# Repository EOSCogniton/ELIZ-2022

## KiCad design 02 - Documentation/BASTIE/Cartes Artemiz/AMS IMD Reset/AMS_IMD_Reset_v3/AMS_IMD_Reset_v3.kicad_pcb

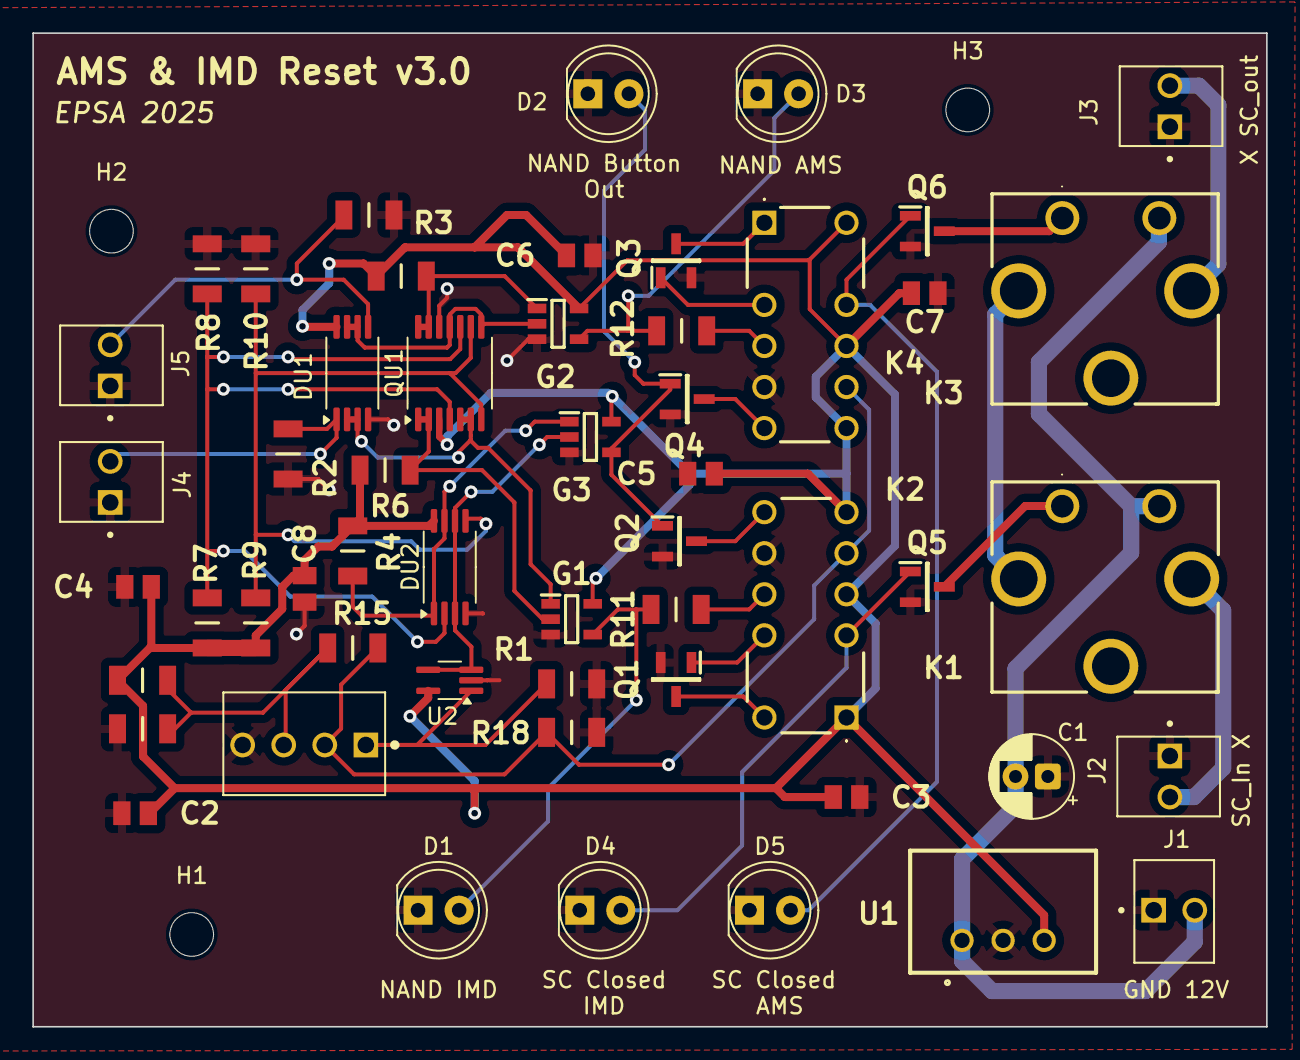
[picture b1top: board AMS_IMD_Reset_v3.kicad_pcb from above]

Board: 2 copper layers, 76.3 x 61.5 mm, 56 parts (0 on the bottom side), 34 nets.

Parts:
C1: C; CP_Radial_D5.0mm_P2.00mm
C2, C3, C4, C5, C6, C7, C8: 1u; CAPC2012X130N
D1, D2, D3, D4, D5: LED; LED_D5.0mm
DU1, DU2: Opamp_Dual; TSSOP-8_4.4x3mm_P0.65mm
G1, G2: Gate NAND SN74AHCT1G00DBVR; SOT95P280X145-5N
G3: Gate AND SN74AHCT1G08DBVR; SOT95P280X145-5N
H1, H2, H3: MountingHole; MountingHole_2.7mm_M2.5
J1, J2, J3, J4, J5: 2P Droit 2-11-2022; MOLEX_22-11-2022
J7: 4P Droit 22-11-2042; MOLEX_22-11-2042
K1, K3: Relais PCB; CP112V
K2, K4: Bistable V23079B1201B301; V23079B1201B301
Q1, Q2, Q3, Q4, Q5, Q6: NMOS SQ2348ES-T1_GE3; SOT95P237X112-3N
QU1: Opamp_Quad; TSSOP-14_4.4x5mm_P0.65mm
R1, R2, R3: 500k; RESC3216X70N
R4, R5, R6: 10k; RESC3216X70N
R7, R10: 82k; RESC3216X70N
R8, R9: 12k; RESC3216X70N
R11, R12: 500; RESC3216X70N
R15: 3k9; RESC3216X70N
R16, R17: 8k2; RESC3216X70N
R18: 100k; RESC3216X70N
U1: Alim LP TSR_0.5-2450; TSR-0.5-2433
U2: SOT-353_SC-70-5_Handsoldering

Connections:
+5V: C2.1, C3.2, C4.2, C5.2, C6.1, C7.1, C8.1, DU1.8 (V+), DU2.8 (V+), G1.5 (VCC), G2.5 (VCC), G3.5 (VCC), K2.1 (COIL1), K2.4 (COM_1), K2.6 (COIL2), K4.7 (COIL2), K4.9 (COM_2), K4.12 (COIL1), QU1.3 (V+), R4.1, R5.2, R6.1, R7.2, R9.2, R16.2, U1.3 (+VOUT), U2.5 (V+)
+12V: C1.2, J1.2, K1.5, K3.5, U1.1 (+VIN)
/0.75V: DU2.2 (-), QU1.4 (-), QU1.10 (-), R7.1, R8.2
/4.25V: DU2.5 (+), QU1.7 (+), QU1.9 (+), R9.1, R10.2
/AMS_OK: DU1.6 (-), DU1.7, G2.2, QU1.8 (-), QU1.11 (+)
/AMS_SCS_Compliance: G2.1, QU1.13, QU1.14, R5.1
/Button_Input: J7.2, K2.5 (Set_1), K4.8 (Set_2), R15.1, R18.1
/Button_Input_SCS: J7.3, R15.2, R16.1, R17.2
/Button_Output: DU2.3 (+), DU2.6 (-), G3.2, U2.3 (-), U2.4
/Button_Output_SCS_Compliance: DU2.1, DU2.7, G3.1, R4.2
/IMD_OK: DU1.2 (-), DU1.3, G1.1, QU1.5 (+), QU1.6 (-)
/IMD_SCS_Compliance: G1.2, QU1.1, QU1.2, R6.2
/Raw_AMS_OK: DU1.5 (+), J5.2, R3.1
/Raw_Button_Output: J7.1, R1.1, U2.1 (+)
/Raw_IMD_OK: DU1.1 (+), J4.2, R2.1
/SC in: J2.2, K1.4
/SC out: J3.2, K3.4
/SC_Closed_AMS: D5.2 (A), K4.10 (Reset_2), Q6.1
/SC_Closed_IMD: D4.2 (A), K2.3 (Reset_1), Q5.1
GND: C1.1, C2.2, C3.1, C4.1, C5.1, C6.2, C7.2, C8.2, D1.1 (K), D2.1 (K), D3.1 (K), D4.1 (K), D5.1 (K), DU1.4 (V-), DU2.4 (V-), G1.3 (GND), G2.3 (GND), G3.3 (GND), J1.1, J2.1, J3.1, J4.1, J5.1, J7.4, K2.8 (Set_2), K4.5 (Set_1), Q1.2, Q2.2, Q3.2, Q4.2, Q5.2, Q6.2, QU1.12 (V-), R1.2, R2.2, R3.2, R8.1, R10.1, R17.1, R18.2, U1.2 (GND), U2.2 (V-)
unnamed: D1.2 (A), G1.4, R11.1
unnamed: D2.2 (A), G3.4, Q2.1, Q4.1
unnamed: D3.2 (A), G2.4, R12.1
unnamed: K1.1, Q5.3
unnamed: K1.2, K3.2
unnamed: K2.12 (COIL1), Q1.3
unnamed: K2.7 (COIL2), Q2.3
unnamed: K2.9 (COM_2), R11.2
unnamed: K2.10 (Reset_2), Q1.1
unnamed: K3.1, Q6.3
unnamed: K4.1 (COIL1), Q3.3
unnamed: K4.6 (COIL2), Q4.3
unnamed: K4.4 (COM_1), R12.2
unnamed: K4.3 (Reset_1), Q3.1

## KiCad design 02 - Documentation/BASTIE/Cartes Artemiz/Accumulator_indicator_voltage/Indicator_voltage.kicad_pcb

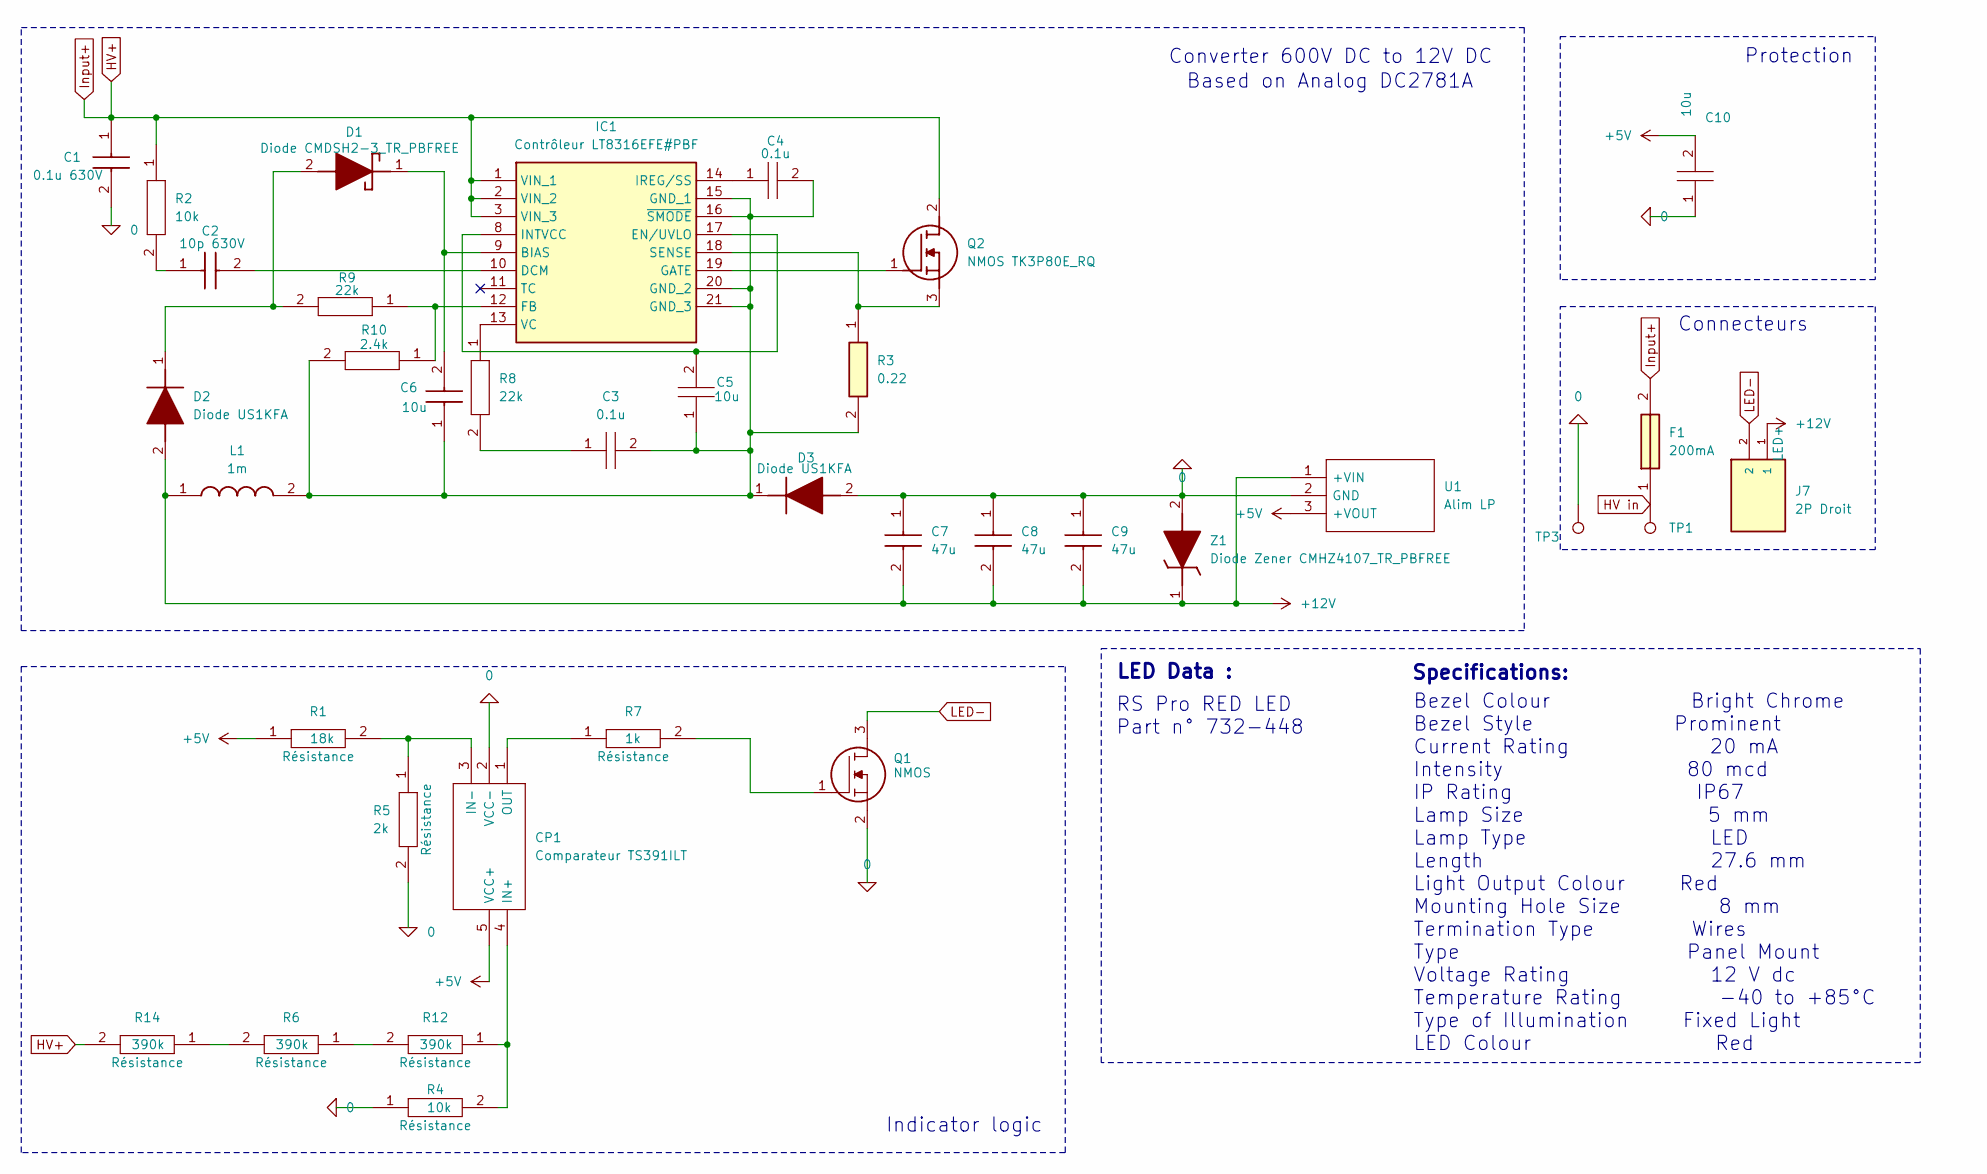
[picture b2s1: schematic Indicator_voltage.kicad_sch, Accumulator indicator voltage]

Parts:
C1: 0.1u 630V; CAPC4532X200N; Mouser Part Number 81-GCJ43DR72J104KX1L
C2: 10p 630V; CAPC3216X100N; Mouser Part Number 81-GRM31A5C2J100JW1D
C3, C4: 0.1u; CAPC2012X130N; Manufacturer_Part_Number 0805Y1000104JXT
C5, C10: 10u; CAPC2012X130N; Manufacturer_Part_Number 0805Y1000104JXT
C6: 10u; GRM31x; Manufacturer_Part_Number GRM31CR71E106KA12L; Mouser Part Number 81-GRM31CR71E106KA12
C7, C8, C9: 47u; CAPC3225X270N; Mouser Part Number 81-GRM32ER61C476KE5K
CP1: Comparateur TS391ILT; SOT95P280X145-5N; Manufacturer_Part_Number TS391ILT; Mouser Part Number 511-TS391IL
D1: Diode CMDSH2-3_TR_PBFREE; SOD2512X110N; Mouser Part Number 610-CMDSH2-3
D2, D3: Diode US1KFA; SODFL3618X143N; Mouser Part Number 512-US1KFA
F1: 200mA; 0ADAP0200RE; Mouser Part Number 530-0ADAP0200-RE
IC1: Contrôleur LT8316EFE#PBF; LT8315EFEPBF; Mouser Part Number 584-LT8316EFE#PBF
J7: 2P Droit 2-11-2022; MOLEX_22-11-2022; PARTREV BD8; Mouser Part Number 538-22-11-2022
L1: 1m; WE-PD_1260_1245_1280_121054; Mouser Part Number 710-7447709102
Q1: NMOS SQ2348ES-T1_GE3; SOT95P237X112-3N; Manufacturer_Part_Number SQ2348ES-T1_GE3; Mouser Part Number 781-SQ2348ES-T1_GE3
Q2: NMOS TK3P80E_RQ; TK3P80ERQ; Manufacturer_Part_Number TK3P80E,RQ
R1: 18k; RESC3216X70N; Manufacturer_Part_Number RK73H2BLTDD2152F; Mouser Part Number N/A
R2, R4: 10k; RESC3216X70N; Manufacturer_Part_Number RK73H2BLTDD2152F; Mouser Part Number N/A
R3: 0.22; RESC1608X55N; Mouser Part Number 754-RL0816S-R22-F
R5: 2k; RESC3216X70N; Manufacturer_Part_Number RK73H2BLTDD2152F; Mouser Part Number N/A
R6, R12, R14: 390k; RESC3216X70N; Manufacturer_Part_Number RK73H2BLTDD2152F; Mouser Part Number N/A
R7: 1k; RESC3216X70N; Manufacturer_Part_Number RK73H2BLTDD2152F; Mouser Part Number N/A
R8, R9: 22k; RESC3216X70N; Manufacturer_Part_Number RK73H2BLTDD2152F; Mouser Part Number N/A
R10: 2.4k; RESC3216X70N; Manufacturer_Part_Number RK73H2BLTDD2152F; Mouser Part Number N/A
TP1, TP3: type="R" model="TestPoint" lib=""; SolderWire-2.5sqmm_1x01_D2.4mm_OD3.6mm
U1: Alim LP TSR_0.5-2450; TSR-0.5-2433; Manufacturer_Part_Number TSR 0.5-2450; Mouser Part Number 495-TSR0.5-2450
Z1: Diode Zener CMHZ4107_TR_PBFREE; SOD3816X135N; Manufacturer_Part_Number CMHZ4107 TR PBFREE

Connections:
0: C1.2, C7.1, C8.1, C9.1, C10.1, CP1.2 (VCC-), D3.2 (A), Q1.2, R4.1, R5.2, TP3.1, U1.2 (GND), Z1.2 (A)
+5V: C10.2, CP1.5 (VCC+), R1.1, U1.3 (+VOUT)
+12V: C7.2, C8.2, C9.2, D2.2 (A), J7.1, L1.1, U1.1 (+VIN), Z1.1 (K)
HV in: F1.1, TP1.1
HV+: C1.1, F1.2, IC1.1 (VIN_1), IC1.2 (VIN_2), IC1.3 (VIN_3), Q2.2 (D), R2.1, R14.2
LED-: J7.2, Q1.3
unnamed: C2.1, R2.2
unnamed: C3.1, R8.2
unnamed: CP1.4 (IN+), R4.2, R12.1
unnamed: CP1.3 (IN-), R1.2, R5.1
unnamed: CP1.1 (OUT), R7.1
unnamed: D1.2 (A), D2.1 (K), R9.2
unnamed: C6.2, D1.1 (K), IC1.9 (BIAS)
unnamed: C3.2, C4.2, C5.1, C6.1, D3.1 (K), IC1.15 (GND_1), IC1.16 (~SMODE), IC1.20 (GND_2), IC1.21 (GND_3), L1.2, R3.2, R10.2
unnamed: C2.2, IC1.10 (DCM)
unnamed: C5.2, IC1.8 (INTVCC), IC1.17 (EN/UVLO)
unnamed: IC1.12 (FB), R9.1, R10.1
unnamed: IC1.19 (GATE), Q2.1 (G)
unnamed: C4.1, IC1.14 (IREG/SS)
unnamed: IC1.18 (SENSE), Q2.3 (S), R3.1
unnamed: IC1.13 (VC), R8.1
unnamed: Q1.1, R7.2
unnamed: R6.1, R12.2
unnamed: R6.2, R14.1

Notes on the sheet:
Protection
Based on Analog DC2781A
RS Pro RED LED Part n° 732-448
Indicator logic
LED Data :
Specifications:
Connecteurs
Converter 600V DC to 12V DC
Bezel Colour Bright Chrome Bezel Style Prominent Current Rating 20 mA Intensity 80 mcd IP Rating IP67 Lamp Size 5 mm Lamp Type LED Length 27.6 mm Light Output Colour Red Mounting Hole Size 8 mm Termination Type Wires Type Panel Mount Voltage Rating 12 V dc Temperature Rating -40 to +85°C Type of Il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

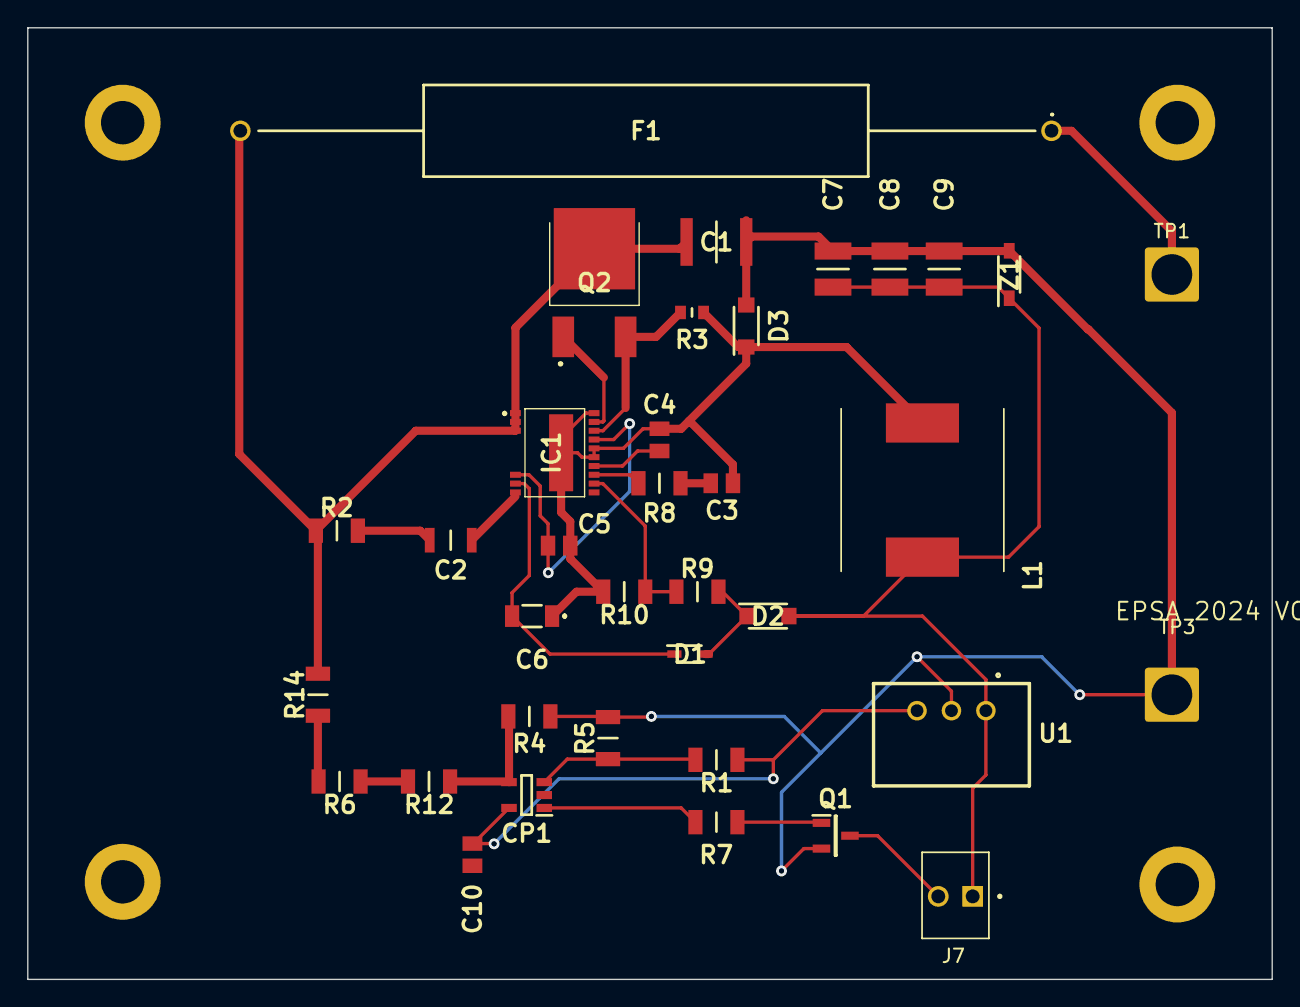
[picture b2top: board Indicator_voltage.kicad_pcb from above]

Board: 2 copper layers, 91.8 x 70.2 mm, 36 parts (0 on the bottom side), 24 nets.

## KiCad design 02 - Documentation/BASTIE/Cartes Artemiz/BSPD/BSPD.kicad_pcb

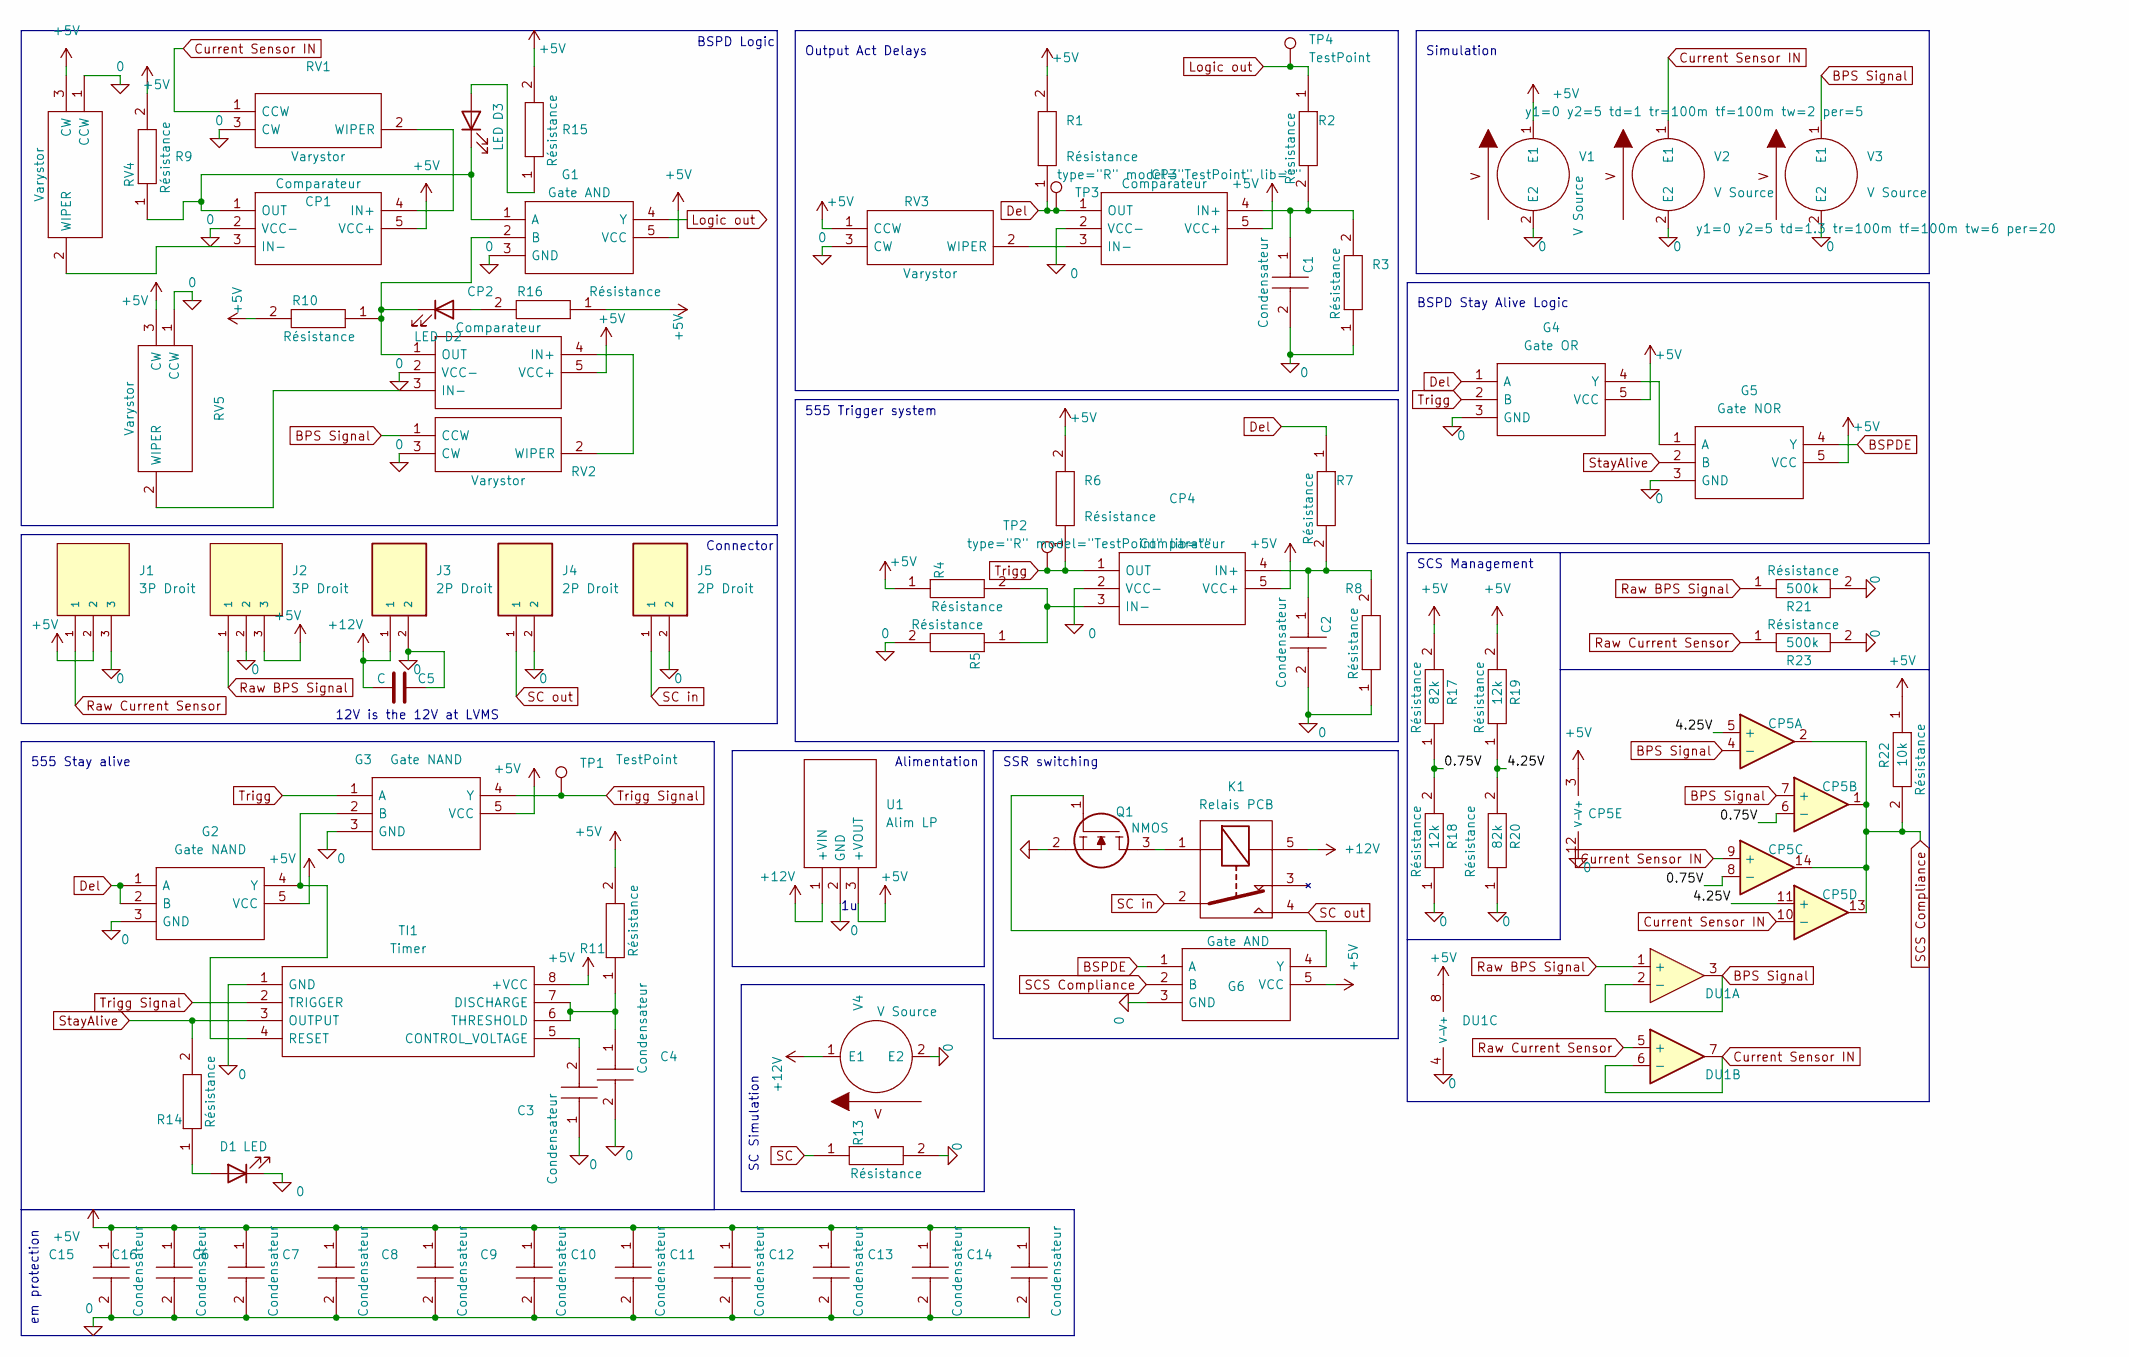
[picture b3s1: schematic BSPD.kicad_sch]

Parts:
C1, C2, C3, C4, C6, C7, C8, C9, C10, C11, C12, C13, C14, C15, C16: Condensateur 0805Y1000104JXT; CAPC2012X130N; Manufacturer_Part_Number 0805Y1000104JXT
C5: C; CP_Radial_D5.0mm_P2.00mm
CP1, CP2, CP3, CP4: Comparateur TS391ILT; SOT95P280X145-5N; Manufacturer_Part_Number TS391ILT; Mouser Part Number 511-TS391IL
CP5: Opamp_Quad; TSSOP-14_4.4x5mm_P0.65mm; Manufacturer_Part_Number LMV339IPWR; Mouser Part Number 595-LMV339IPWR
D1, D2, D3: LED; LED_D5.0mm
DU1: Opamp_Dual; TSSOP-8_4.4x3mm_P0.65mm; Manufacturer_Part_Number TLV9062QPWRQ1; Mouser Part Number 595-TLV9062QPWRQ1
G1, G6: Gate AND SN74AHCT1G08DBVR; SOT95P280X145-5N; Manufacturer_Part_Number SN74AHCT1G08DBVR; Mouser Part Number 595-SN74AHCT1G08DBVR
G2, G3: Gate NAND SN74AHCT1G00DBVR; SOT95P280X145-5N; Manufacturer_Part_Number SN74AHCT1G00DBVR; Mouser Part Number 595-SN74AHCT1G00DBVR
G4: Gate OR SN74AHCT1G32DBVR; SOT95P280X145-5N; Manufacturer_Part_Number SN74AHCT1G32DBVR; Mouser Part Number 595-SN74AHCT1G32DBVR
G5: Gate NOR SN74AHCT1G02DBVR; SOT95P280X145-5N; Manufacturer_Part_Number SN74AHCT1G02DBVR; Mouser Part Number 595-SN74AHCT1G02DBVR
J1, J2: 3P Droit 22-11-2032; MOLEX_22-11-2032; PARTREV BD8
J3, J4, J5: 2P Droit 2-11-2022; MOLEX_22-11-2022; PARTREV BD8
K1: Relais PCB; CP112V; Mouser Part Number 769-CP1-12V
Q1: NMOS SQ2348ES-T1_GE3; SOT95P237X112-3N; Manufacturer_Part_Number SQ2348ES-T1_GE3; Mouser Part Number 781-SQ2348ES-T1_GE3
R1, R2, R3, R4, R5, R6, R7, R8, R9, R10, R11, R13, R14, R15, R16: Résistance RK73H2BLTDD2152F; RESC3216X70N; Manufacturer_Part_Number RK73H2BLTDD2152F; Mouser Part Number N/A
R17, R20: 82k; RESC3216X70N; Manufacturer_Part_Number RK73H2BLTDD2152F; Mouser Part Number N/A
R18, R19: 12k; RESC3216X70N; Manufacturer_Part_Number RK73H2BLTDD2152F; Mouser Part Number N/A
R21, R23: 500k; RESC3216X70N; Manufacturer_Part_Number RK73H2BLTDD2152F; Mouser Part Number N/A
R22: 10k; RESC3216X70N; Manufacturer_Part_Number RK73H2BLTDD2152F; Mouser Part Number N/A
RV1, RV2, RV3, RV4, RV5: Varystor 3296Y-1-223LF; 3296Y1223LF; Manufacturer_Part_Number 3296Y-1-223LF; Mouser Part Number 652-3296Y-1-223LF
TI1: Timer 555 LM555CMX_NOPB; DIP-8_W7.62mm_Socket; Manufacturer_Part_Number LM555CMX/NOPB; Mouser Part Number 926-LM555CMX/NOPB
TP1, TP4: TestPoint; TestPoint_Pad_D2.0mm
TP2, TP3: type="R" model="TestPoint" lib=""; TestPoint_Pad_D2.0mm
U1: Alim LP TSR_0.5-2450; TSR-0.5-2433; Manufacturer_Part_Number TSR 0.5-2450; Mouser Part Number 495-TSR0.5-2450
V1: 5
V2, V3: VSOURCE
V4: 12

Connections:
0: C1.2, C2.2, C3.1, C4.2, C5.2, C6.2, C7.2, C8.2, C9.2, C10.2, C11.2, C12.2, C13.2, C14.2, C15.2, C16.2, CP1.2 (VCC-), CP2.2 (VCC-), CP3.2 (VCC-), CP4.2 (VCC-), CP5.12 (V-), D1.1 (K), DU1.4 (V-), G1.3 (GND), G2.3 (GND), G3.3 (GND), G4.3 (GND), G5.3 (GND), G6.3 (GND), J1.3, J2.2, J3.2, J4.2, J5.2, R3.1, R5.2, R8.1, R18.1, R20.1, R21.2, R23.2, RV1.3 (CW), RV2.3 (CW), RV3.3 (CW), RV4.1 (CCW), RV5.1 (CCW), TI1.1 (GND), U1.2 (GND)
+5V: C6.1, C7.1, C8.1, C9.1, C10.1, C11.1, C12.1, C13.1, C14.1, C15.1, C16.1, CP1.5 (VCC+), CP2.5 (VCC+), CP3.5 (VCC+), CP4.5 (VCC+), CP5.3 (V+), DU1.8 (V+), G1.5 (VCC), G2.5 (VCC), G3.5 (VCC), G4.5 (VCC), G5.5 (VCC), G6.5 (VCC), J1.2, J2.3, R1.2, R4.1, R6.2, R9.2, R10.2, R11.2, R15.2, R16.1, R17.2, R19.2, R22.1, RV3.1 (CCW), RV4.3 (CW), RV5.3 (CW), TI1.8 (+VCC), U1.3 (+VOUT)
+12V: C5.1, J3.1, K1.5, U1.1 (+VIN), V4.1 (E1)
/0.75V: CP5.6 (-), CP5.8 (-), R17.1, R18.2
/4.25V: CP5.5 (+), CP5.11 (+), R19.1, R20.2
BPS Signal: CP5.4 (-), CP5.7 (+), DU1.2 (-), DU1.3, RV2.1 (CCW), V3.1 (E1)
BSPDE: G5.4 (Y), G6.1 (A)
Current Sensor IN: CP5.9 (+), CP5.10 (-), DU1.6 (-), DU1.7, RV1.1 (CCW), V2.1 (E1)
Del: CP3.1 (OUT), G2.1 (A), G2.2 (B), G4.1 (A), R1.1, R7.1, TP3.1
GND: Q1.2
Logic out: G1.4 (Y), R2.1, TP4.1
unnamed: CP1.4 (IN+), RV1.2 (WIPER)
unnamed: CP1.3 (IN-), RV4.2 (WIPER)
unnamed: CP1.1 (OUT), D3.1 (K), G1.1 (A), R9.1
unnamed: CP2.4 (IN+), RV2.2 (WIPER)
unnamed: CP2.3 (IN-), RV5.2 (WIPER)
unnamed: CP2.1 (OUT), D2.1 (K), G1.2 (B), R10.1
unnamed: C1.1, CP3.4 (IN+), R2.2, R3.2
unnamed: CP3.3 (IN-), RV3.2 (WIPER)
unnamed: C2.1, CP4.4 (IN+), R7.2, R8.2
unnamed: CP4.3 (IN-), R4.2, R5.1
unnamed: D1.2 (A), R14.1
unnamed: D2.2 (A), R16.2
unnamed: D3.2 (A), R15.1
unnamed: G2.4 (Y), G3.2 (B), TI1.4 (RESET)
unnamed: G4.4 (Y), G5.1 (A)
unnamed: G6.4 (Y), Q1.1
unnamed: K1.1, Q1.3
unnamed: C3.2, TI1.5 (CONTROL_VOLTAGE)
unnamed: C4.1, R11.1, TI1.6 (THRESHOLD), TI1.7 (DISCHARGE)
Raw BPS Signal: DU1.1 (+), J2.1, R21.1
Raw Current Sensor: DU1.5 (+), J1.1, R23.1
SC in: J5.1, K1.2
SC out: J4.1, K1.4
SCS Compliance: CP5.1, CP5.2, CP5.13, CP5.14, G6.2 (B), R22.2
StayAlive: G5.2 (B), R14.2, TI1.3 (OUTPUT)
Trigg: CP4.1 (OUT), G3.1 (A), G4.2 (B), R6.1, TP2.1
Trigg Signal: G3.4 (Y), TI1.2 (TRIGGER), TP1.1

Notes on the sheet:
em protection
BSPD Stay Alive Logic
12V is the 12V at LVMS
SSR switching
SCS Management
Simulation
Connector
BSPD Logic
555 Trigger system
SC Simulation
Output Act Delays
555 Stay alive
Alimentation

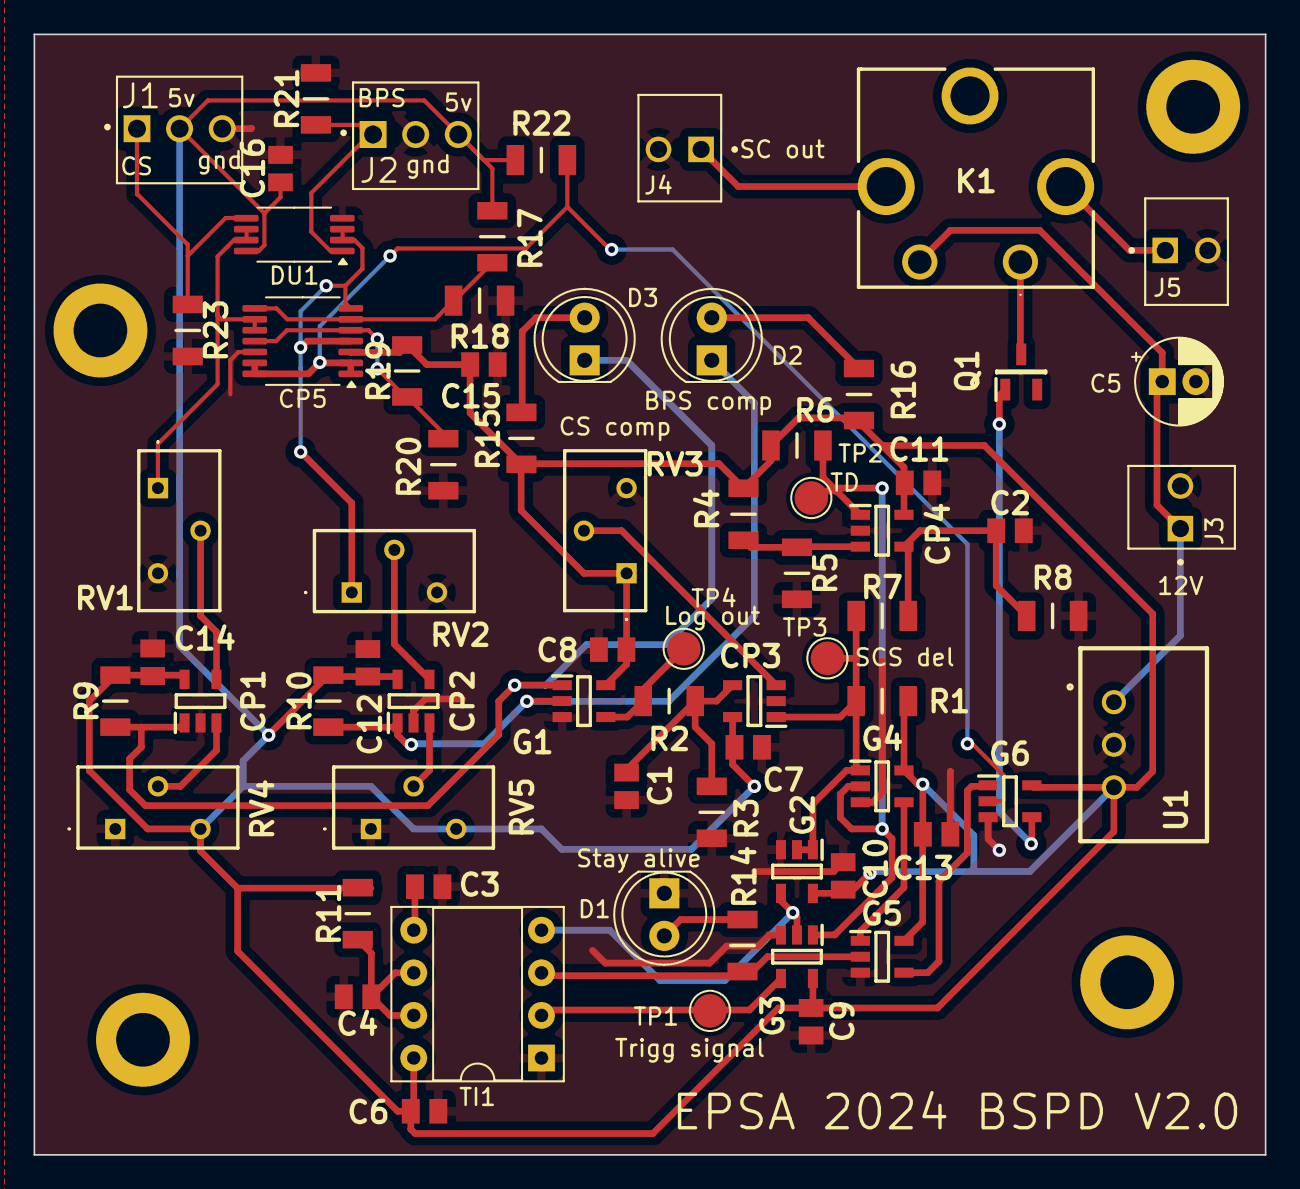
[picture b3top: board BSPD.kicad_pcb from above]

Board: 2 copper layers, 73.4 x 66.8 mm, 70 parts (0 on the bottom side), 37 nets.

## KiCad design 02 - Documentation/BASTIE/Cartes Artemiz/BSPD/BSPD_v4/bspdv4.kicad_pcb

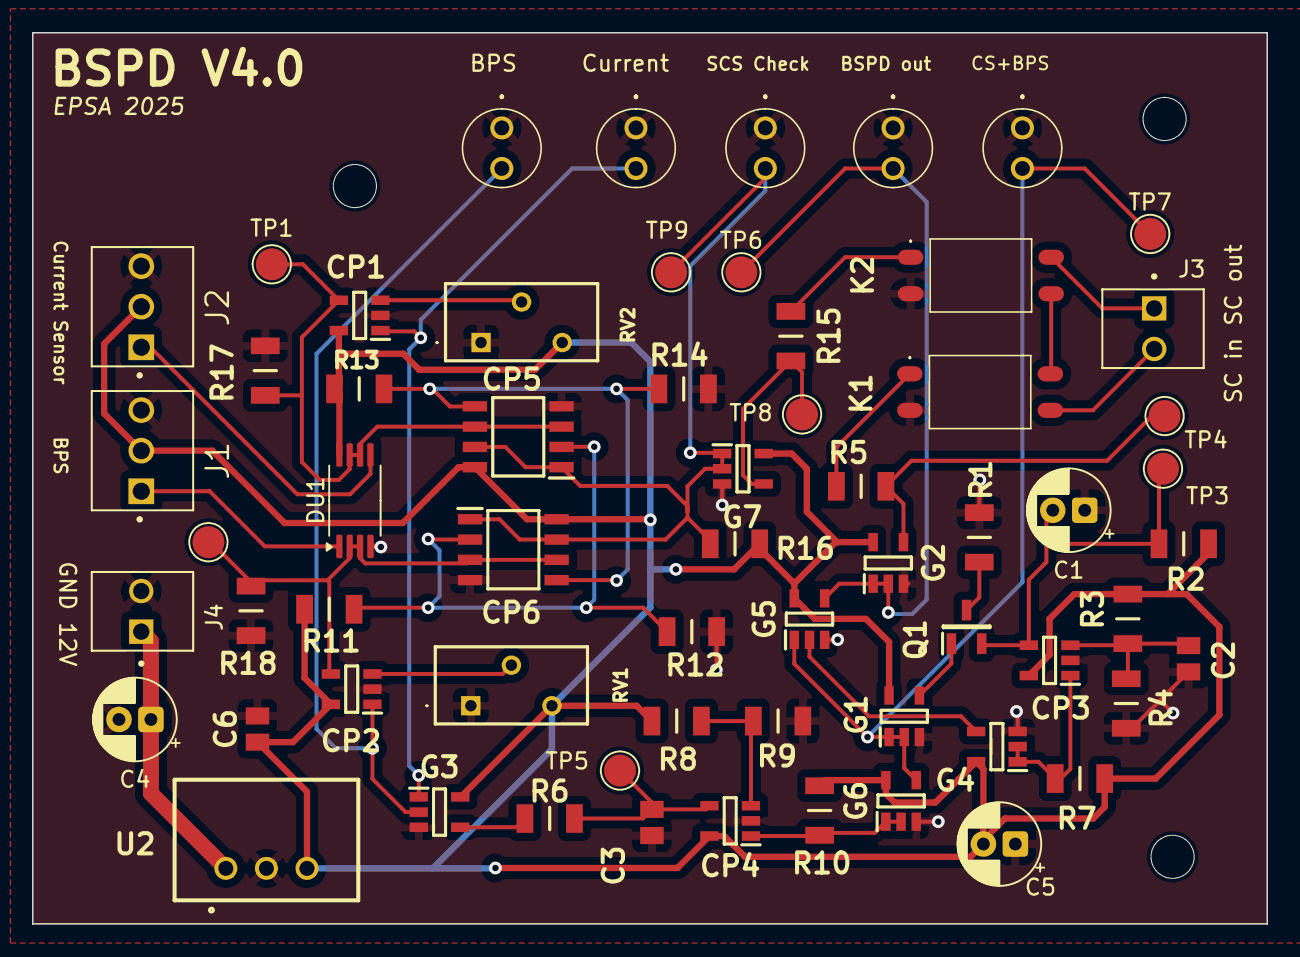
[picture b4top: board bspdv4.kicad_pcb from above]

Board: 2 copper layers, 77.3 x 55.8 mm, 65 parts (0 on the bottom side), 33 nets.

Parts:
C1, C4, C5: 10u; CP_Radial_D5.0mm_P2.00mm
C2: 10n; CAPC2012X130N
C3: 1u; CAPC2012X130N
C6: 0.1u; CAPC2012X130N
CP1, CP2, CP3, CP4: Comparateur TS391ILT; SOT95P280X145-5N
CP5, CP6: Comparateur Double LM393LVDR; SOIC127P600X175-8N
DU1: Opamp_Dual; TSSOP-8_4.4x3mm_P0.65mm
G1, G2, G4, G7: Gate NAND SN74AHCT1G00DBVR; SOT95P280X145-5N
G3, G6: Gate AND SN74AHCT1G08DBVR; SOT95P280X145-5N
G5: Gate OR SN74AHCT1G32DBVR; SOT95P280X145-5N
H1, H2, H3: MountingHole; MountingHole_2.7mm_M2.5
J1, J2: 3P Droit 22-11-2032; MOLEX_22-11-2032
J3, J4: 2P Droit 2-11-2022; MOLEX_22-11-2022
K1, K2: SSR CPC1394GR; CPC1394GR
LED1, LED2, LED3, LED4, LED5: LED 5mm; 4302H55V
Q1: PMOS SI2343CDS-T1-GE3; SOT95P237X112-3N
R1: 200; RESC3216X70N
R2, R6: 1M; RESC3216X70N
R3, R7, R8: 10k; RESC3216X70N
R4: 56k; RESC3216X70N
R5, R15: 470; RESC3216X70N
R9, R10, R16: 47k; RESC3216X70N
R11, R14: 82K; RESC3216X70N
R12, R13: 12K; RESC3216X70N
R17, R18: 470k; RESC3216X70N
RV1, RV2: Varystor 3296Y-1-223LF; 3296Y1223LF
TP1, TP2, TP3, TP4, TP5, TP6, TP7, TP8, TP9: type="R" model="TestPoint" lib=""; TestPoint_Pad_D2.0mm
U2: Alim LP TSR_0.5-2450; TSR-0.5-2433

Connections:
0.75V: CP5.2 (IN1-), CP6.2 (IN1-), R11.2, R12.1
4.25V: CP5.5 (IN2+), CP6.5 (IN2+), R13.2, R14.1
+5V: C5.2, C6.2, CP1.5 (VCC+), CP2.5 (VCC+), CP3.5 (VCC+), CP4.5 (VCC+), CP5.8 (V+), CP6.8 (V+), DU1.8 (V+), G1.5 (VCC), G2.5 (VCC), G3.5 (VCC), G4.5 (VCC), G5.5 (VCC), G6.5 (VCC), G7.5 (VCC), J1.2, J2.2, R2.2, R3.2, R7.1, R8.2, R10.1, R11.1, R13.1, R16.1, RV1.3 (CW), RV2.3 (CW), U2.3 (+VOUT)
+12V: C4.1, J4.1, U2.1 (+VIN)
BPS signal: CP2.4 (IN+), CP6.3 (IN1+), CP6.6 (IN2-), DU1.2 (-), DU1.3, R18.1, TP2.1
BSPD out: G2.1, G2.2, G5.4, LED2.2 (A), TP6.1
Current Sensor: CP1.4 (IN+), CP5.3 (IN1+), CP5.6 (IN2-), DU1.6 (-), DU1.7, R17.1, TP1.1
GND: C1.1, C2.1, C3.2, C4.2, C5.1, C6.1, CP1.2 (VCC-), CP2.2 (VCC-), CP3.2 (VCC-), CP4.2 (VCC-), CP5.4 (GND), CP6.4 (GND), DU1.4 (V-), G1.3 (GND), G2.3 (GND), G3.3 (GND), G4.3 (GND), G5.3 (GND), G6.3 (GND), G7.3 (GND), J1.3, J2.3, J4.2, K1.2 (-_CONTROL), K2.2 (-_CONTROL), LED1.1 (K), LED2.1 (K), LED3.1 (K), LED4.1 (K), LED5.1 (K), R1.1, R4.1, R9.1, R12.2, R14.2, R17.2, R18.2, RV1.1 (CCW), RV2.1 (CCW), U2.2 (GND)
Intput w/ 50msdelay: G1.1, G1.2, G5.1, G6.4, LED1.2 (A), TP7.1
unnamed: CP1.3 (IN-), RV2.2 (WIPER)
unnamed: CP1.1 (OUT), G3.1, LED5.2 (A)
unnamed: CP2.3 (IN-), RV1.2 (WIPER)
unnamed: CP2.1 (OUT), G3.2, LED3.2 (A)
unnamed: C1.2, CP3.4 (IN+), Q1.2, R2.1, TP3.1
unnamed: C2.2, CP3.3 (IN-), R3.1, R4.2
unnamed: CP3.1 (OUT), G4.1, G4.2, R7.2
unnamed: C3.1, CP4.4 (IN+), R6.2, TP5.1
unnamed: CP4.3 (IN-), R8.1, R9.2
unnamed: CP4.1 (OUT), G6.1, G6.2, R10.2
unnamed: G1.4, Q1.1
unnamed: G2.4, R5.1, TP4.1
unnamed: G3.4, R6.1
unnamed: G4.4, G5.2
unnamed: G7.4, R15.1, TP8.1
unnamed: K1.1 (+_CONTROL), R5.2
unnamed: K2.1 (+_CONTROL), R15.2
unnamed: Q1.3, R1.2
Raw BPS Signal: DU1.1 (+), J1.1
Raw Current Sensor: DU1.5 (+), J2.1
SC in: J3.1, K2.4 (LOAD_2)
SC out: J3.2, K1.3 (LOAD_1)
SCS Check: CP5.1 (OUT1), CP5.7 (OUT2), CP6.1 (OUT1), CP6.7 (OUT2), G7.1, G7.2, LED4.2 (A), R16.2, TP9.1
SCS relay: K1.4 (LOAD_2), K2.3 (LOAD_1)
